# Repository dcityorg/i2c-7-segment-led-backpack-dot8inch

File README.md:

#### I²C 7 Segment LED Backpack Board (.8 inch LEDs)

<div style="text-align: center;">
<div style="display: inline-block; margin-right: 5px;">

</div>
<div style="display: inline-block; margin-right: 5px;">

</div>
<div style="display: inline-block; margin-right: 5px;">

</div>
</div>

**[This link has details](https://www.dcity.org/portfolio/i2c-7-segment-led-backpack-dot8inch) including**
* parts lists
* assembly instructions
* jumper configuration
* Arduino, Particle and Raspberry Pi software library usage
* Bare PC boards are available from OSHPark.

**Note: The pictures show the backpack board with Grove type connectors, but they have been changed to [Qwiic](https://www.sparkfun.com/qwiic) connectors.**

**License Information**
Open Source Hardware Design. Our License Information is [here](https://www.dcity.org/license-information/).

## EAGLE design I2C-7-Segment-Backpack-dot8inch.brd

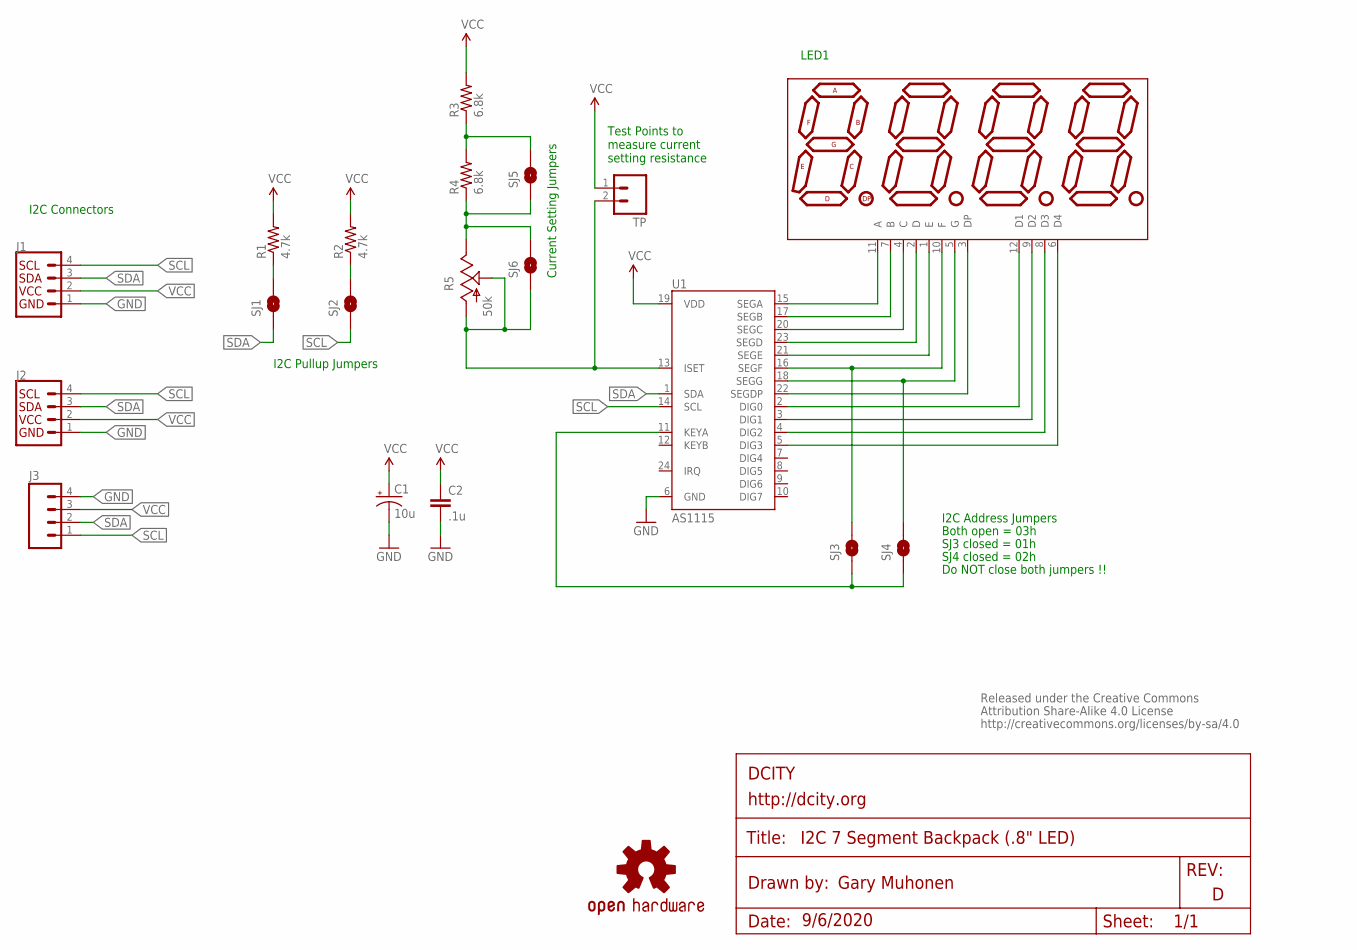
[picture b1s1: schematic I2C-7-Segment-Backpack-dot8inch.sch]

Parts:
C1: 10u; 0805-POL
C2: .1u; 0805-CAP
DISP1: LED1; 7-SEGMENT-4DIGIT-COUNTER-NO-SILK
J1, J2: QWIIC_RIGHT_ANGLE; JST04_1MM_RA
J3: M04LOCK; 1X04_LOCK
LOGO1: OSHW-LOGOS; OSHW-LOGO-S
R1, R2: 4.7k; 0805-RES
R3, R4: 6.8k; 0805-RES
R5: 50k; POT-TC33X
SJ1, SJ2, SJ3, SJ4, SJ5, SJ6: SOLDERJUMPERNO; SJ_2S-NO
TP: M02PTH; 1X02
U1: AS1115; TSSOP-24
U$2: CREATIVE_COMMONS

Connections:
GND: C1.-, C2.2, J1.1, J2.1, J3.4, U1.6 (GND)
unnamed: DISP1.11 (A), U1.15 (SEGA)
unnamed: DISP1.7 (B), U1.17 (SEGB)
unnamed: DISP1.4 (C), U1.20 (SEGC)
unnamed: DISP1.2 (D), U1.23 (SEGD)
unnamed: DISP1.1 (E), U1.21 (SEGE)
unnamed: DISP1.10 (F), SJ3.2, U1.16 (SEGF)
unnamed: DISP1.5 (G), SJ4.2, U1.18 (SEGG)
unnamed: DISP1.3 (DP), U1.22 (SEGDP)
unnamed: DISP1.12 (D1), U1.2 (DIG0)
unnamed: DISP1.9 (D2), U1.3 (DIG1)
unnamed: DISP1.8 (D3), U1.4 (DIG2)
unnamed: DISP1.6 (D4), U1.5 (DIG3)
unnamed: SJ3.1, SJ4.1, U1.11 (KEYA)
unnamed: R5.1 (A), R5.2 (S), SJ6.1, TP.2, U1.13 (ISET)
unnamed: R4.1, R5.3 (E), SJ5.1, SJ6.2
unnamed: R3.1, R4.2, SJ5.2
unnamed: R1.1, SJ1.2
unnamed: R2.1, SJ2.2
SCL: J1.4, J2.4, J3.1, SJ2.1, U1.14 (SCL)
SDA: J1.3, J2.3, J3.2, SJ1.1, U1.1 (SDA)
VCC: C1.+, C2.1, J1.2, J2.2, J3.3, R1.2, R2.2, R3.2, TP.1, U1.19 (VDD)

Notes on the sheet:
I2C Connectors
I2C Pullup Jumpers
Current Setting Jumpers
I2C Address Jumpers
Both open = 03h
SJ3 closed = 01h
SJ4 closed = 02h
Do NOT close both jumpers !!
LED1
Test Points to measure current setting resistance

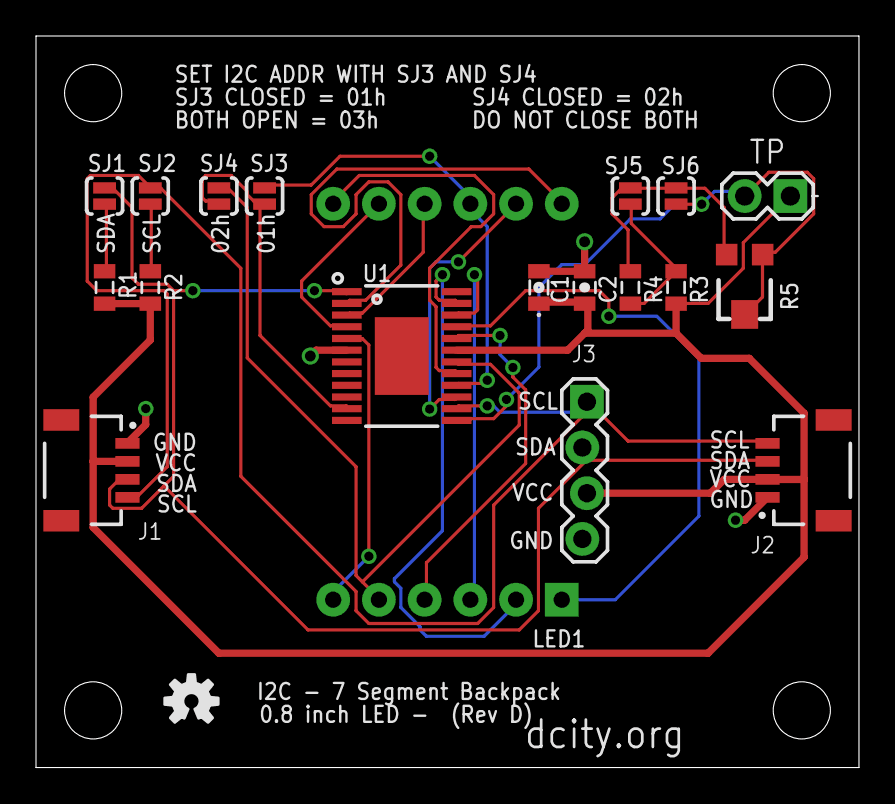
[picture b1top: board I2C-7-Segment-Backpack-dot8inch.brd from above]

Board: 2 copper layers, 45.7 x 40.6 mm, 21 parts (1 on the bottom side), 22 nets.

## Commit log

2016-07-30 First commit - Rev B
2018-09-14 Rev C
2018-09-14 fixed readme.md
2020-10-11 Rev D

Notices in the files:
parts and their libraries:
0: Released under the Creative Commons
0: http://creativecommons.org/licenses/by-sa/4.0
